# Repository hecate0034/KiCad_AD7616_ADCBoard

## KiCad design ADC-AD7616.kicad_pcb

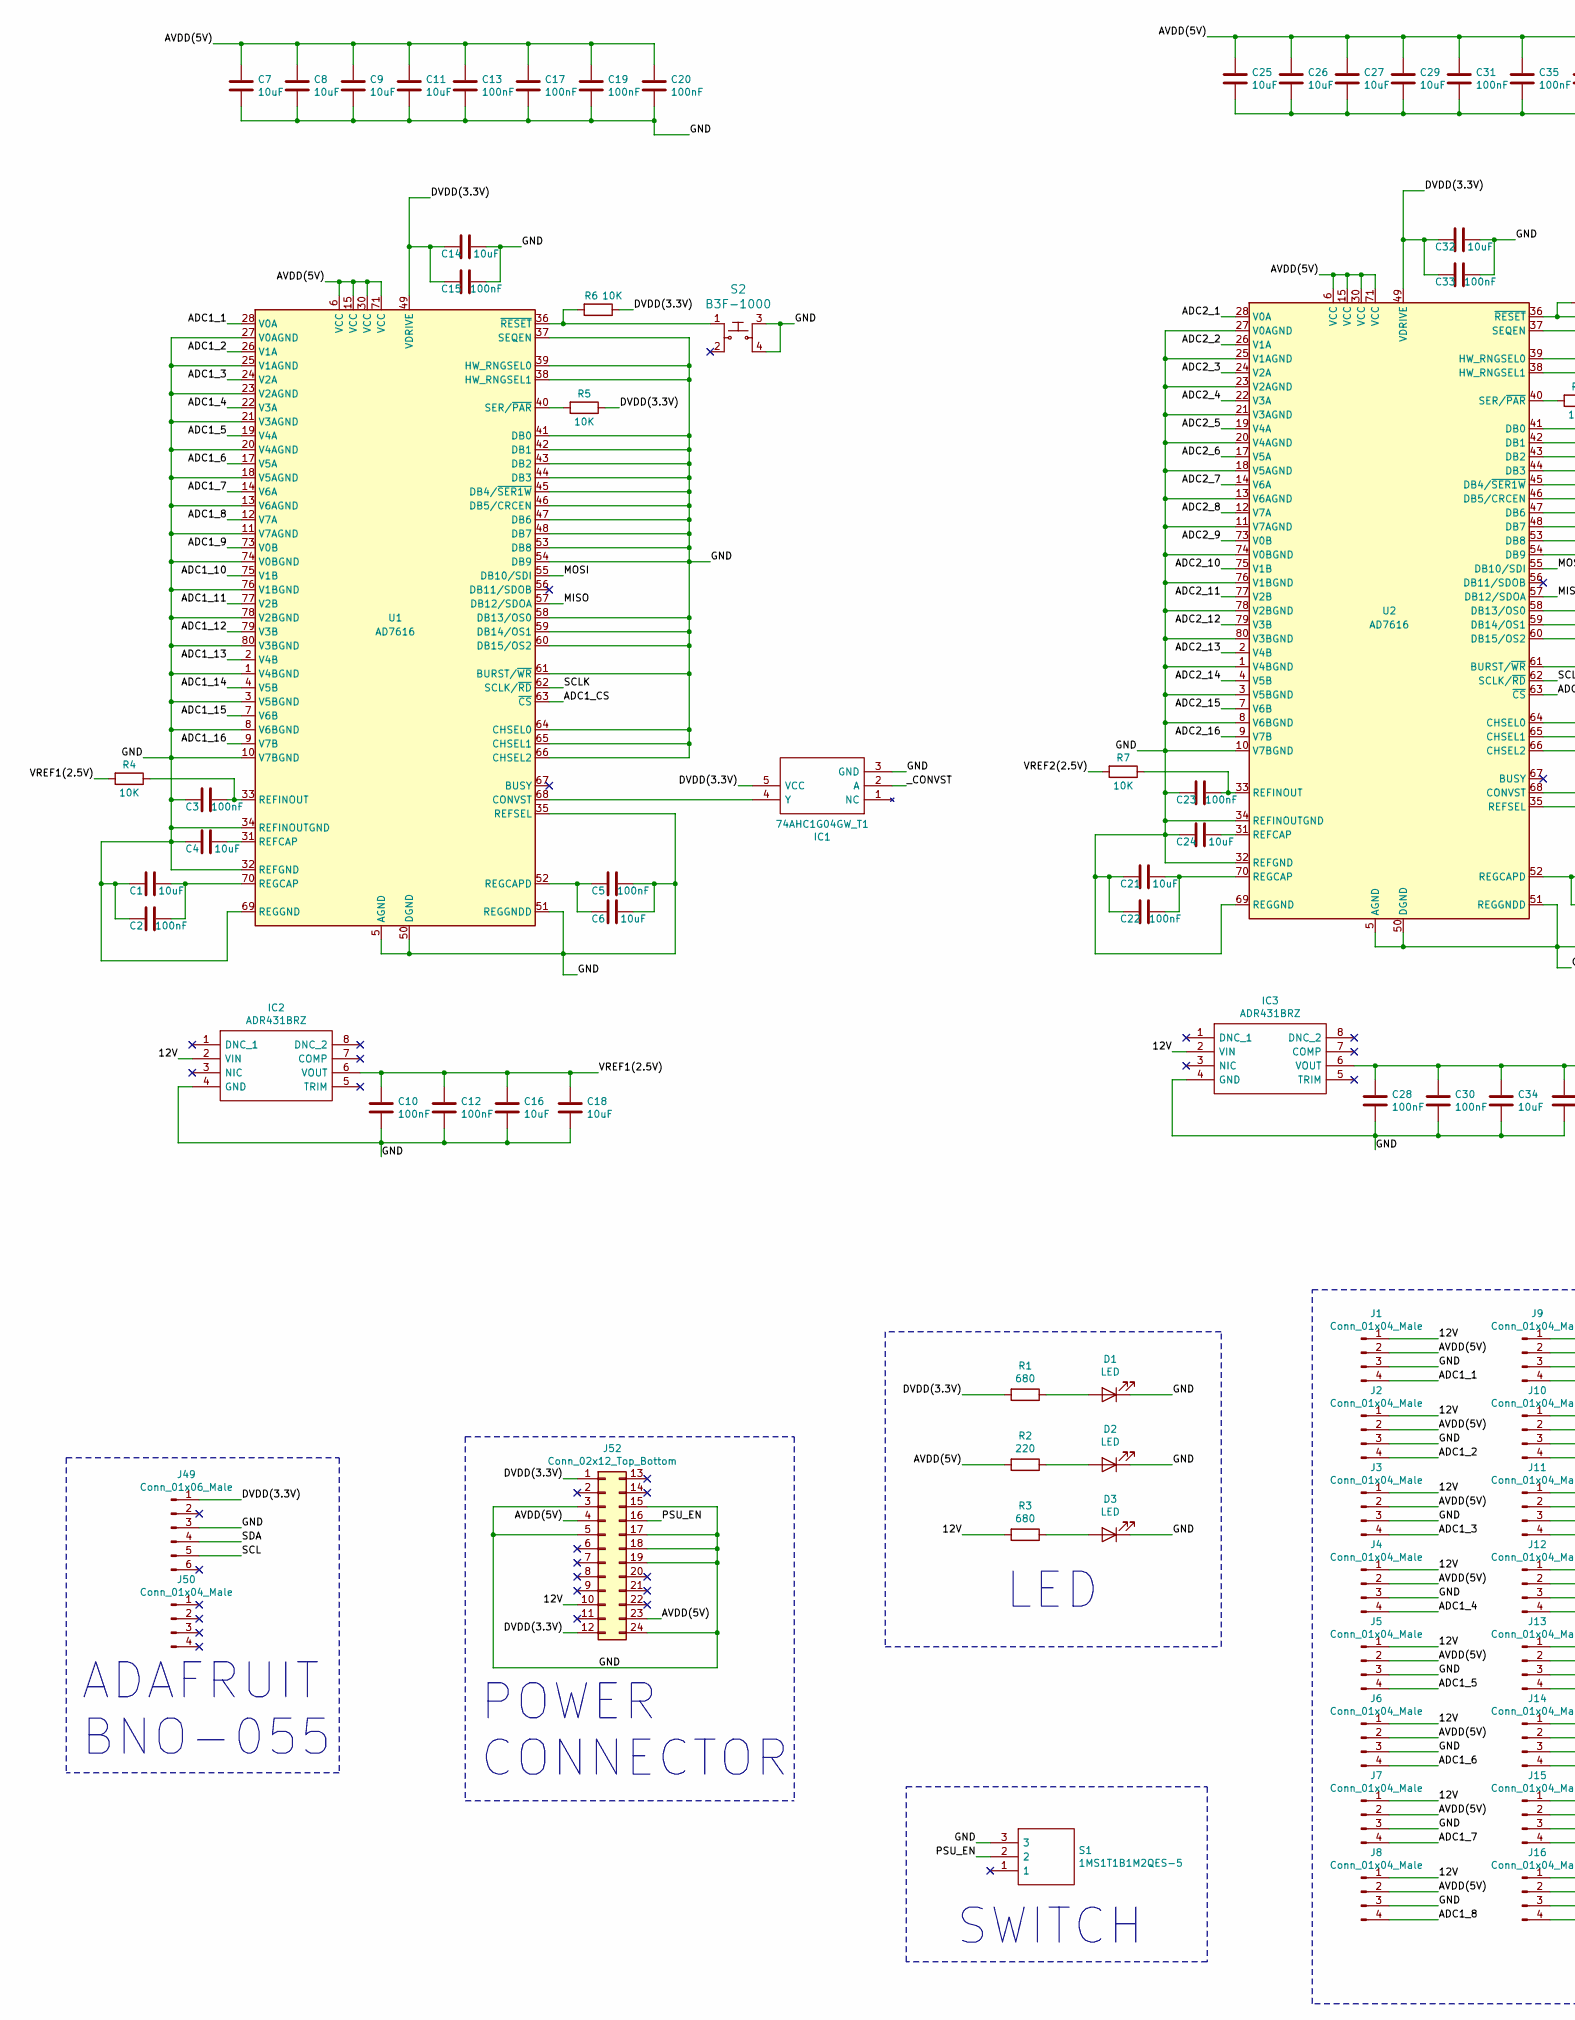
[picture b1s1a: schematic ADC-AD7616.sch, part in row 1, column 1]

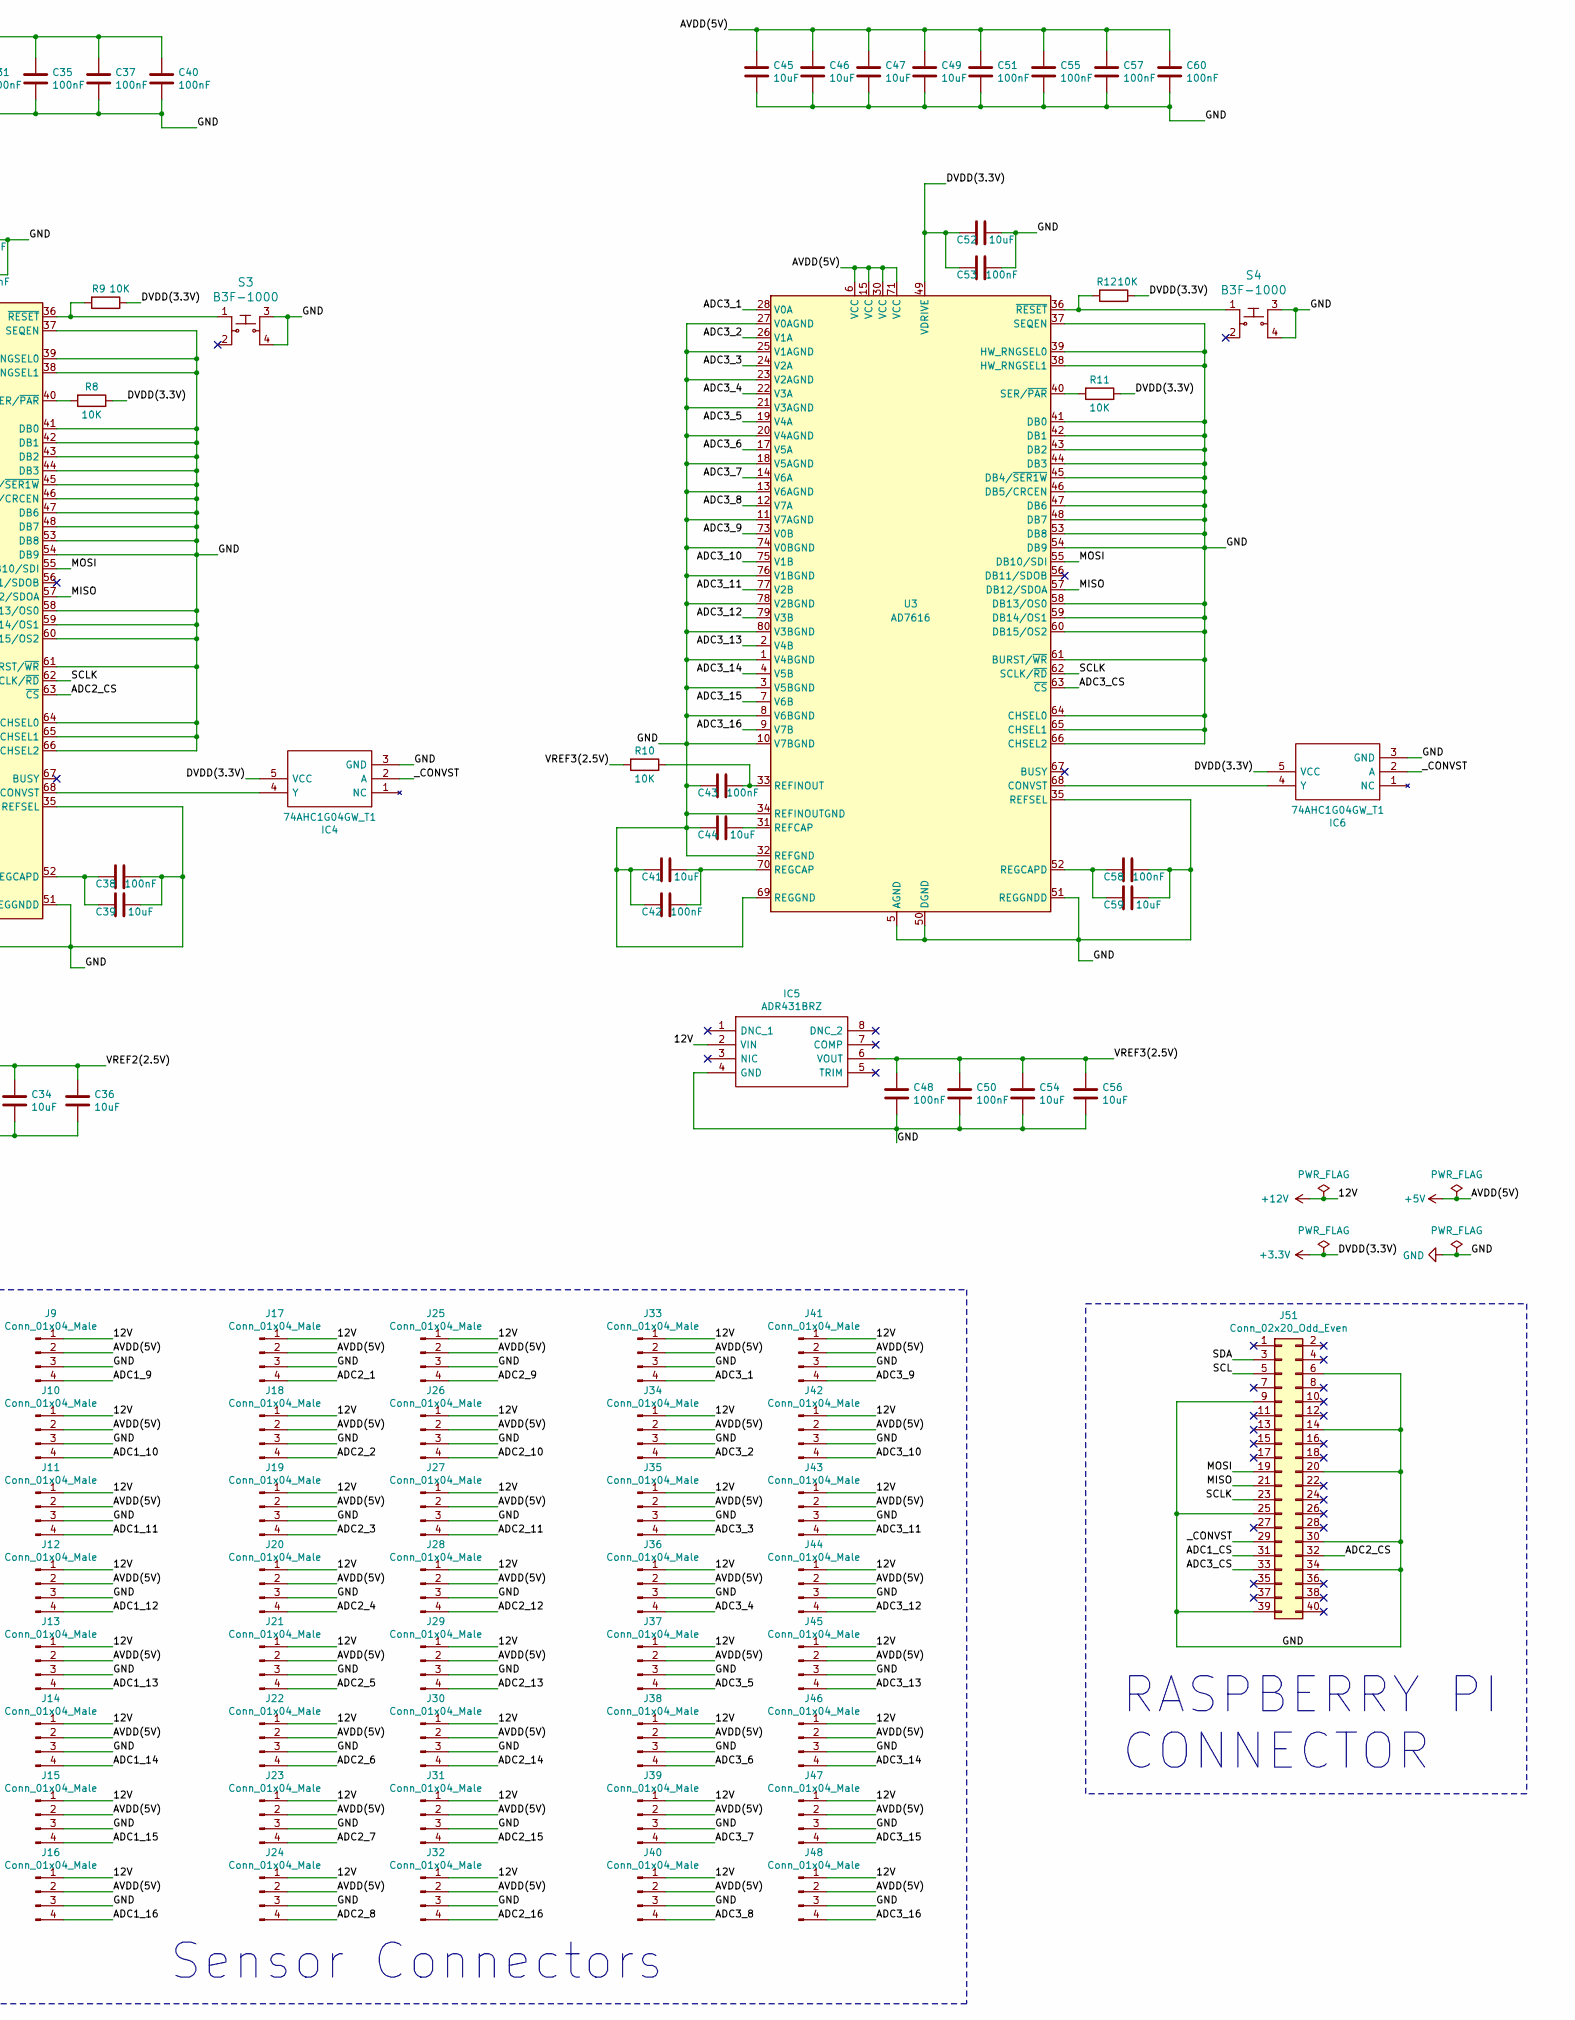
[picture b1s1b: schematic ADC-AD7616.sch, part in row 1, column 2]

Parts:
C1, C4, C6, C7, C8, C9, C11, C14, C16, C18, C21, C24, C25, C26, C27, C29, C32, C34, C36, C39, C41, C44, C45, C46, C47, C49, C52, C54, C56, C59: 10uF; C_1206_3216Metric
C2, C3, C5, C10, C12, C13, C15, C17, C19, C20, C22, C23, C28, C30, C31, C33, C35, C37, C38, C40, C42, C43, C48, C50, C51, C53, C55, C57, C58, C60: 100nF; C_0603_1608Metric
D1, D2, D3: LED; LED_0603_1608Metric
IC1, IC4, IC6: 74AHC1G04GW_T1; SOT65P212X110-5N; Manufacturer_Part_Number 74AHC1G04GW/T1
IC2, IC3, IC5: ADR431BRZ; Manufacturer_Part_Number ADR431BRZ; Mouser Part Number 584-ADR431BRZ
J1, J2, J3, J4, J5, J6, J7, J8, J9, J10, J11, J12, J13, J14, J15, J16, J17, J18, J19, J20, J21, J22, J23, J24, J25, J26, J27, J28, J29, J30, J31, J32, J33, J34, J35, J36, J37, J38, J39, J40, J41, J42, J43, J44, J45, J46, J47, J48: Conn_01x04_Male; JST_PH_B4B-PH-K_1x04_P2.00mm_Vertical
J49: Conn_01x06_Male; PinSocket_1x06_P2.54mm_Vertical
J50: Conn_01x04_Male; PinSocket_1x04_P2.54mm_Vertical
J51: Conn_02x20_Odd_Even; PinSocket_2x20_P2.54mm_Vertical
J52: Conn_02x12_Top_Bottom; Molex_Mini-Fit_Jr_5566-24A2_2x12_P4.20mm_Vertical
R1, R3: 680; R_0805_2012Metric
R2: 220; R_0805_2012Metric
R4, R5, R6, R7, R8, R9, R10, R11, R12: 10K; R_0603_1608Metric
S1: 1MS1T1B1M2QES-5; Manufacturer_Part_Number 1MS1T1B1M2QES-5
S2, S3, S4: B3F-1000; B3F1002; MPN B3F-1000; Digi-Key_PN SW400-ND
U1, U2, U3: AD7616; LQFP-80_14x14mm_P0.65mm

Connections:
+3V3: C14.2, C15.2, C32.2, C33.2, C52.2, C53.2, IC1.5 (VCC), IC4.5 (VCC), IC6.5 (VCC), J49.1, J52.1, J52.12, R1.2, R5.1, R6.1, R8.1, R9.1, R11.1, R12.1, U1.49 (VDRIVE), U2.49 (VDRIVE), U3.49 (VDRIVE)
+5V: C7.1, C8.1, C9.1, C11.1, C13.1, C17.1, C19.1, C20.1, C25.1, C26.1, C27.1, C29.1, C31.1, C35.1, C37.1, C40.1, C45.1, C46.1, C47.1, C49.1, C51.1, C55.1, C57.1, C60.1, J1.2, J2.2, J3.2, J4.2, J5.2, J6.2, J7.2, J8.2, J9.2, J10.2, J11.2, J12.2, J13.2, J14.2, J15.2, J16.2, J17.2, J18.2, J19.2, J20.2, J21.2, J22.2, J23.2, J24.2, J25.2, J26.2, J27.2, J28.2, J29.2, J30.2, J31.2, J32.2, J33.2, J34.2, J35.2, J36.2, J37.2, J38.2, J39.2, J40.2, J41.2, J42.2, J43.2, J44.2, J45.2, J46.2, J47.2, J48.2, J52.4, J52.23, R2.2, U1.6 (VCC), U1.15 (VCC), U1.30 (VCC), U1.71 (VCC), U2.6 (VCC), U2.15 (VCC), U2.30 (VCC), U2.71 (VCC), U3.6 (VCC), U3.15 (VCC), U3.30 (VCC), U3.71 (VCC)
+12V: IC2.2 (VIN), IC3.2 (VIN), IC5.2 (VIN), J1.1, J2.1, J3.1, J4.1, J5.1, J6.1, J7.1, J8.1, J9.1, J10.1, J11.1, J12.1, J13.1, J14.1, J15.1, J16.1, J17.1, J18.1, J19.1, J20.1, J21.1, J22.1, J23.1, J24.1, J25.1, J26.1, J27.1, J28.1, J29.1, J30.1, J31.1, J32.1, J33.1, J34.1, J35.1, J36.1, J37.1, J38.1, J39.1, J40.1, J41.1, J42.1, J43.1, J44.1, J45.1, J46.1, J47.1, J48.1, J52.10, R3.2
/ADC1_1: J1.4, U1.28 (V0A)
/ADC1_2: J2.4, U1.26 (V1A)
/ADC1_3: J3.4, U1.24 (V2A)
/ADC1_4: J4.4, U1.22 (V3A)
/ADC1_5: J5.4, U1.19 (V4A)
/ADC1_6: J6.4, U1.17 (V5A)
/ADC1_7: J7.4, U1.14 (V6A)
/ADC1_8: J8.4, U1.12 (V7A)
/ADC1_9: J9.4, U1.73 (V0B)
/ADC1_10: J10.4, U1.75 (V1B)
/ADC1_11: J11.4, U1.77 (V2B)
/ADC1_12: J12.4, U1.79 (V3B)
/ADC1_13: J13.4, U1.2 (V4B)
/ADC1_14: J14.4, U1.4 (V5B)
/ADC1_15: J15.4, U1.7 (V6B)
/ADC1_16: J16.4, U1.9 (V7B)
/ADC1_CS: J51.31, U1.63 (~CS)
/ADC2_1: J17.4, U2.28 (V0A)
/ADC2_2: J18.4, U2.26 (V1A)
/ADC2_3: J19.4, U2.24 (V2A)
/ADC2_4: J20.4, U2.22 (V3A)
/ADC2_5: J21.4, U2.19 (V4A)
/ADC2_6: J22.4, U2.17 (V5A)
/ADC2_7: J23.4, U2.14 (V6A)
/ADC2_8: J24.4, U2.12 (V7A)
/ADC2_9: J25.4, U2.73 (V0B)
/ADC2_10: J26.4, U2.75 (V1B)
/ADC2_11: J27.4, U2.77 (V2B)
/ADC2_12: J28.4, U2.79 (V3B)
/ADC2_13: J29.4, U2.2 (V4B)
/ADC2_14: J30.4, U2.4 (V5B)
/ADC2_15: J31.4, U2.7 (V6B)
/ADC2_16: J32.4, U2.9 (V7B)
/ADC2_CS: J51.32, U2.63 (~CS)
/ADC3_1: J33.4, U3.28 (V0A)
/ADC3_2: J34.4, U3.26 (V1A)
/ADC3_3: J35.4, U3.24 (V2A)
/ADC3_4: J36.4, U3.22 (V3A)
/ADC3_5: J37.4, U3.19 (V4A)
/ADC3_6: J38.4, U3.17 (V5A)
/ADC3_7: J39.4, U3.14 (V6A)
/ADC3_8: J40.4, U3.12 (V7A)
/ADC3_9: J41.4, U3.73 (V0B)
/ADC3_10: J42.4, U3.75 (V1B)
/ADC3_11: J43.4, U3.77 (V2B)
/ADC3_12: J44.4, U3.79 (V3B)
/ADC3_13: J45.4, U3.2 (V4B)
/ADC3_14: J46.4, U3.4 (V5B)
/ADC3_15: J47.4, U3.7 (V6B)
/ADC3_16: J48.4, U3.9 (V7B)
/ADC3_CS: J51.33, U3.63 (~CS)
/MISO: J51.21, U1.57 (DB12/SDOA), U2.57 (DB12/SDOA), U3.57 (DB12/SDOA)
/MOSI: J51.19, U1.55 (DB10/SDI), U2.55 (DB10/SDI), U3.55 (DB10/SDI)
/PSU_EN: J52.16, S1.2
/SCL: J49.5, J51.5
/SCLK: J51.23, U1.62 (SCLK/~RD), U2.62 (SCLK/~RD), U3.62 (SCLK/~RD)
/SDA: J49.4, J51.3
/VREF1(2.5V): C10.1, C12.1, C16.1, C18.1, IC2.6 (VOUT), R4.2
/VREF2(2.5V): C28.1, C30.1, C34.1, C36.1, IC3.6 (VOUT), R7.2
/VREF3(2.5V): C48.1, C50.1, C54.1, C56.1, IC5.6 (VOUT), R10.2
/_CONVST: IC1.2 (A), IC4.2 (A), IC6.2 (A), J51.29
GND: C1.2, C2.2, C3.2, C4.2, C5.1, C6.1, C7.2, C8.2, C9.2, C10.2, C11.2, C12.2, C13.2, C14.1, C15.1, C16.2, C17.2, C18.2, C19.2, C20.2, C21.2, C22.2, C23.2, C24.2, C25.2, C26.2, C27.2, C28.2, C29.2, C30.2, C31.2, C32.1, C33.1, C34.2, C35.2, C36.2, C37.2, C38.1, C39.1, C40.2, C41.2, C42.2, C43.2, C44.2, C45.2, C46.2, C47.2, C48.2, C49.2, C50.2, C51.2, C52.1, C53.1, C54.2, C55.2, C56.2, C57.2, C58.1, C59.1, C60.2, D1.1 (K), D2.1 (K), D3.1 (K), IC1.3 (GND), IC2.4 (GND), IC3.4 (GND), IC4.3 (GND), IC5.4 (GND), IC6.3 (GND), J1.3, J2.3, J3.3, J4.3, J5.3, J6.3, J7.3, J8.3, J9.3, J10.3, J11.3, J12.3, J13.3, J14.3, J15.3, J16.3, J17.3, J18.3, J19.3, J20.3, J21.3, J22.3, J23.3, J24.3, J25.3, J26.3, J27.3, J28.3, J29.3, J30.3, J31.3, J32.3, J33.3, J34.3, J35.3, J36.3, J37.3, J38.3, J39.3, J40.3, J41.3, J42.3, J43.3, J44.3, J45.3, J46.3, J47.3, J48.3, J49.3, J51.6, J51.9, J51.14, J51.20, J51.25, J51.30, J51.34, J51.39, J52.3, J52.5, J52.15, J52.17, J52.18, J52.19, J52.24, S1.3, S2.3, S2.4, S3.3, S3.4, S4.3, S4.4, U1.1 (V4BGND), U1.3 (V5BGND), U1.5 (AGND), U1.8 (V6BGND), U1.10 (V7BGND), U1.11 (V7AGND), U1.13 (V6AGND), U1.16 (AGND), U1.18 (V5AGND), U1.20 (V4AGND), U1.21 (V3AGND), U1.23 (V2AGND), U1.25 (V1AGND), U1.27 (V0AGND), U1.29 (AGND), U1.32 (REFGND), U1.34 (REFINOUTGND), U1.35 (REFSEL), U1.37 (SEQEN), U1.38 (HW_RNGSEL1), U1.39 (HW_RNGSEL0), U1.41 (DB0), U1.42 (DB1), U1.43 (DB2), U1.44 (DB3), U1.45 (DB4/~SER1W), U1.46 (DB5/CRCEN), U1.47 (DB6), U1.48 (DB7), U1.50 (DGND), U1.51 (REGGNDD), U1.53 (DB8), U1.54 (DB9), U1.58 (DB13/OS0), U1.59 (DB14/OS1), U1.60 (DB15/OS2), U1.61 (BURST/~WR), U1.64 (CHSEL0), U1.65 (CHSEL1), U1.66 (CHSEL2), U1.69 (REGGND), U1.72 (AGND), U1.74 (V0BGND), U1.76 (V1BGND), U1.78 (V2BGND), U1.80 (V3BGND), U2.1 (V4BGND), U2.3 (V5BGND), U2.5 (AGND), U2.8 (V6BGND), U2.10 (V7BGND), U2.11 (V7AGND), U2.13 (V6AGND), U2.16 (AGND), U2.18 (V5AGND), U2.20 (V4AGND), U2.21 (V3AGND), U2.23 (V2AGND), U2.25 (V1AGND), U2.27 (V0AGND), U2.29 (AGND), U2.32 (REFGND), U2.34 (REFINOUTGND), U2.35 (REFSEL), U2.37 (SEQEN), U2.38 (HW_RNGSEL1), U2.39 (HW_RNGSEL0), U2.41 (DB0), U2.42 (DB1), U2.43 (DB2), U2.44 (DB3), U2.45 (DB4/~SER1W), U2.46 (DB5/CRCEN), U2.47 (DB6), U2.48 (DB7), U2.50 (DGND), U2.51 (REGGNDD), U2.53 (DB8), U2.54 (DB9), U2.58 (DB13/OS0), U2.59 (DB14/OS1), U2.60 (DB15/OS2), U2.61 (BURST/~WR), U2.64 (CHSEL0), U2.65 (CHSEL1), U2.66 (CHSEL2), U2.69 (REGGND), U2.72 (AGND), U2.74 (V0BGND), U2.76 (V1BGND), U2.78 (V2BGND), U2.80 (V3BGND), U3.1 (V4BGND), U3.3 (V5BGND), U3.5 (AGND), U3.8 (V6BGND), U3.10 (V7BGND), U3.11 (V7AGND), U3.13 (V6AGND), U3.16 (AGND), U3.18 (V5AGND), U3.20 (V4AGND), U3.21 (V3AGND), U3.23 (V2AGND), U3.25 (V1AGND), U3.27 (V0AGND), U3.29 (AGND), U3.32 (REFGND), U3.34 (REFINOUTGND), U3.35 (REFSEL), U3.37 (SEQEN), U3.38 (HW_RNGSEL1), U3.39 (HW_RNGSEL0), U3.41 (DB0), U3.42 (DB1), U3.43 (DB2), U3.44 (DB3), U3.45 (DB4/~SER1W), U3.46 (DB5/CRCEN), U3.47 (DB6), U3.48 (DB7), U3.50 (DGND), U3.51 (REGGNDD), U3.53 (DB8), U3.54 (DB9), U3.58 (DB13/OS0), U3.59 (DB14/OS1), U3.60 (DB15/OS2), U3.61 (BURST/~WR), U3.64 (CHSEL0), U3.65 (CHSEL1), U3.66 (CHSEL2), U3.69 (REGGND), U3.72 (AGND), U3.74 (V0BGND), U3.76 (V1BGND), U3.78 (V2BGND), U3.80 (V3BGND)
unnamed: C1.1, C2.1, U1.70 (REGCAP)
unnamed: C3.1, R4.1, U1.33 (REFINOUT)
unnamed: C4.1, U1.31 (REFCAP)
unnamed: C5.2, C6.2, U1.52 (REGCAPD)
unnamed: C21.1, C22.1, U2.70 (REGCAP)
unnamed: C23.1, R7.1, U2.33 (REFINOUT)
unnamed: C24.1, U2.31 (REFCAP)
unnamed: C38.2, C39.2, U2.52 (REGCAPD)
unnamed: C41.1, C42.1, U3.70 (REGCAP)
unnamed: C43.1, R10.1, U3.33 (REFINOUT)
unnamed: C44.1, U3.31 (REFCAP)
unnamed: C58.2, C59.2, U3.52 (REGCAPD)
unnamed: D1.2 (A), R1.1
unnamed: D2.2 (A), R2.1
unnamed: D3.2 (A), R3.1
unnamed: IC1.4 (Y), U1.68 (CONVST)
unnamed: IC4.4 (Y), U2.68 (CONVST)
unnamed: IC6.4 (Y), U3.68 (CONVST)
unnamed: R5.2, U1.40 (SER/~PAR)
unnamed: R6.2, S2.1, U1.36 (~RESET)
unnamed: R8.2, U2.40 (SER/~PAR)
unnamed: R9.2, S3.1, U2.36 (~RESET)
unnamed: R11.2, U3.40 (SER/~PAR)
unnamed: R12.2, S4.1, U3.36 (~RESET)

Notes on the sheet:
Sensor Connectors
ADAFRUIT BNO-055
LED
RASPBERRY PI CONNECTOR
POWER CONNECTOR
SWITCH

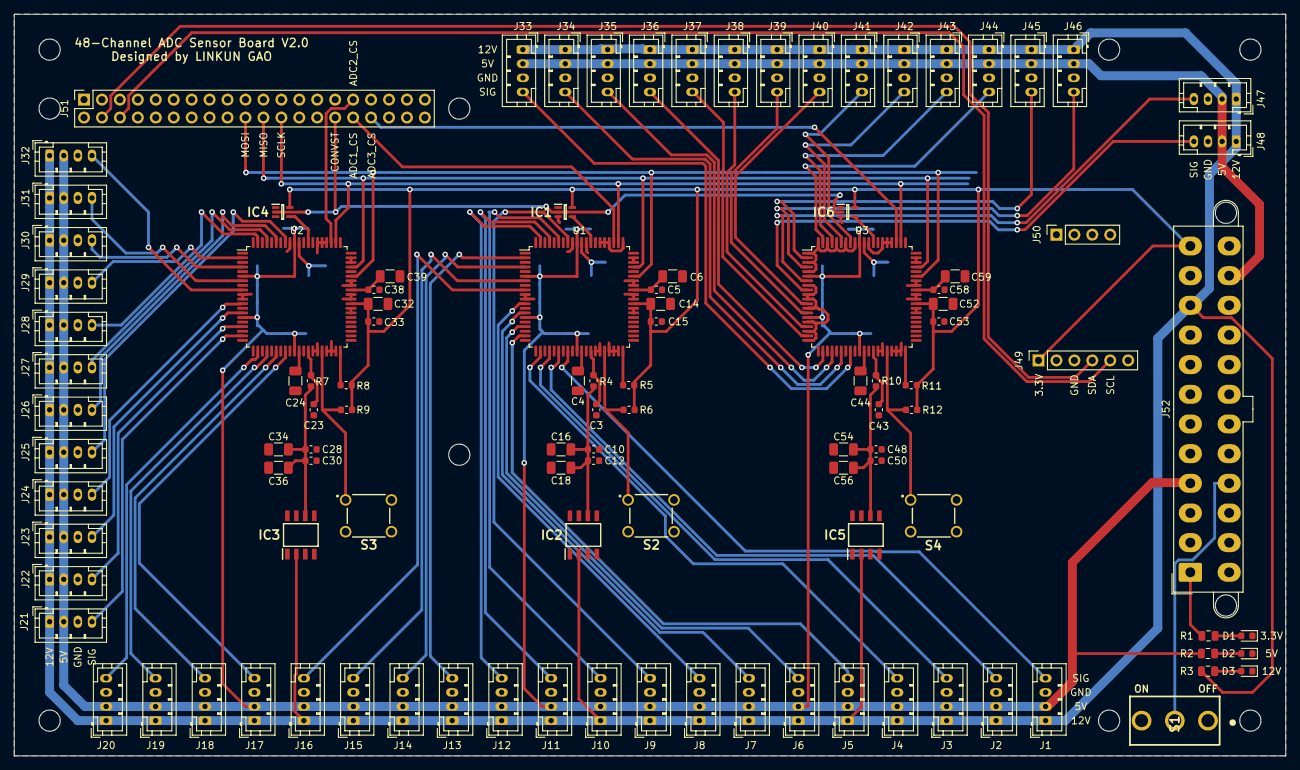
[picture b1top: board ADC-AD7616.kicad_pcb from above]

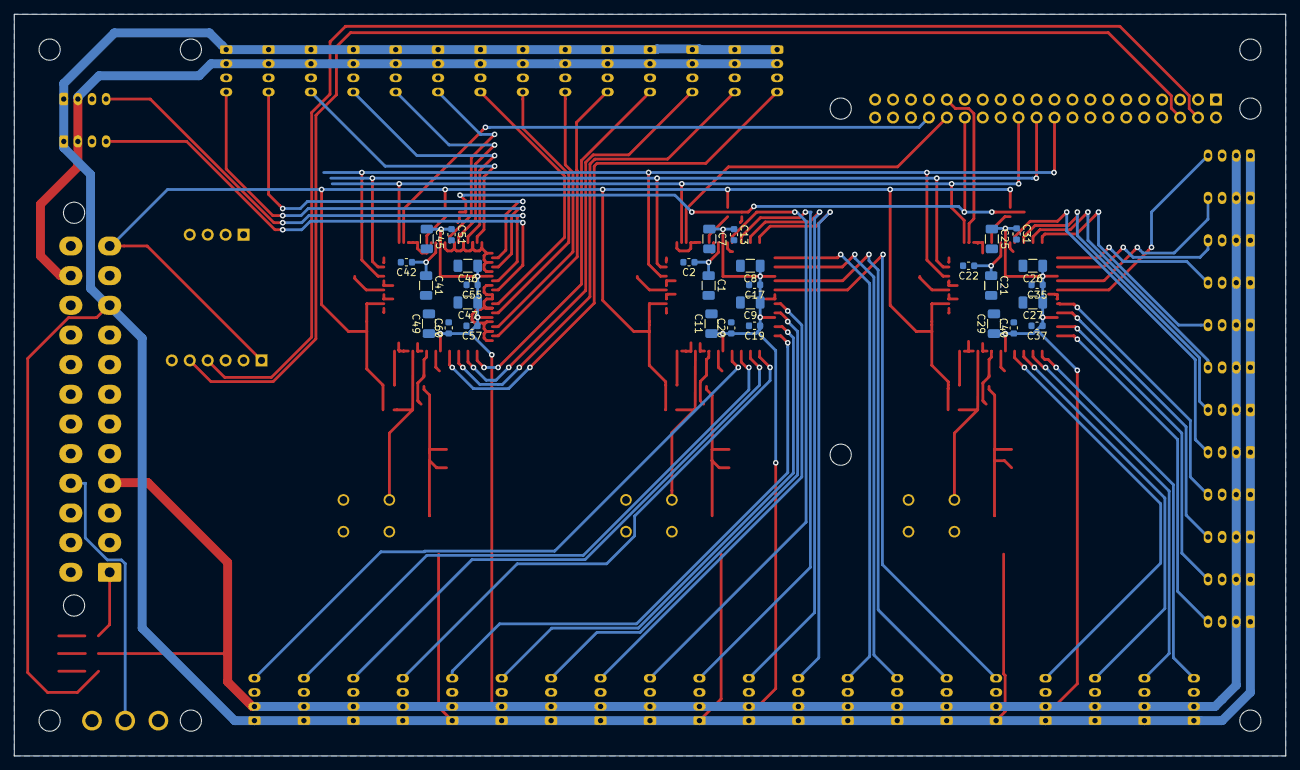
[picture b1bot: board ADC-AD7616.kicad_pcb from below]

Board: 2 copper layers, 180.0 x 105.0 mm, 140 parts (30 on the bottom side), 89 nets.
